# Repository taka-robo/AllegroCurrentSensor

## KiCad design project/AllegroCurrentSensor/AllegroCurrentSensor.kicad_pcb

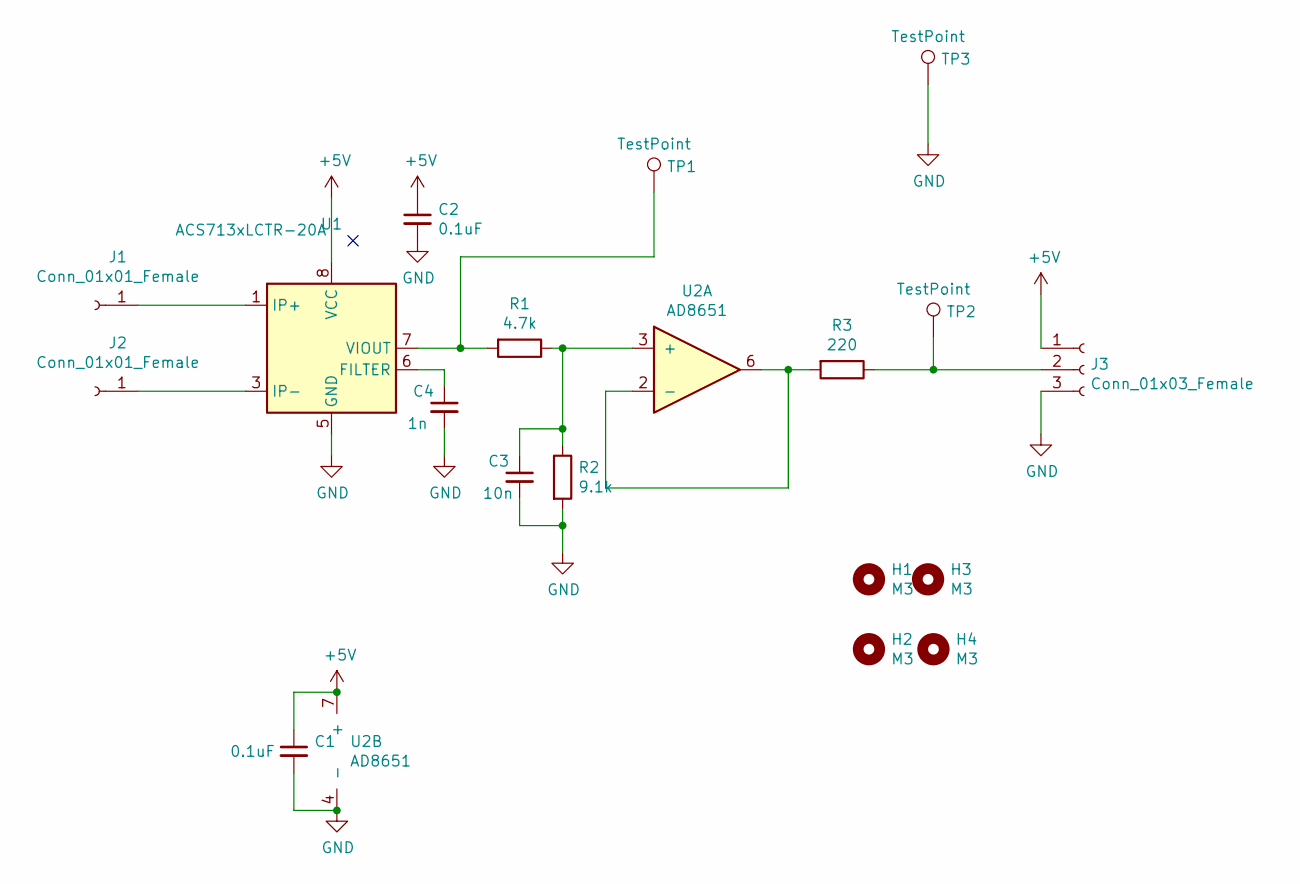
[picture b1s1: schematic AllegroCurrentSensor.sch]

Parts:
C1, C2: 0.1uF; C_0603_1608Metric_Pad1.08x0.95mm_HandSolder
C3: 10n; C_0603_1608Metric_Pad1.08x0.95mm_HandSolder
C4: 1n; C_0603_1608Metric_Pad1.08x0.95mm_HandSolder
H1, H2, H3, H4: M3; MountingHole_3.2mm_M3
J1, J2: Conn_01x01_Female; TestPoint_Pad_4.0x4.0mm
J3: Conn_01x03_Female; PinHeader_1x03_P2.54mm_Vertical
R1: 4.7k; R_0603_1608Metric_Pad0.98x0.95mm_HandSolder
R2: 9.1k; R_0603_1608Metric_Pad0.98x0.95mm_HandSolder
R3: 220; R_0603_1608Metric_Pad0.98x0.95mm_HandSolder
TP1, TP2, TP3: TestPoint; Pin_D0.7mm_L6.5mm_W1.8mm_FlatFork
U1: ACS713xLCTR-20A; SOIC-8_3.9x4.9mm_P1.27mm
U2: AD8651; SOIC-8_3.9x4.9mm_P1.27mm

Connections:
+5V: C1.1, C2.1, J3.1, U1.8 (VCC), U2.7 (+)
GND: C1.2, C2.2, C3.2, C4.2, J3.3, R2.2, TP3.1, U1.5 (GND), U2.4 (-)
unnamed: C3.1, R1.1, R2.1, U2.3 (+)
unnamed: C4.1, U1.6 (FILTER)
unnamed: J1.1, U1.1 (IP+), U1.2 (IP+)
unnamed: J2.1, U1.3 (IP-), U1.4 (IP-)
unnamed: J3.2, R3.1, TP2.1
unnamed: R1.2, TP1.1, U1.7 (VIOUT)
unnamed: R3.2, U2.2 (-), U2.6

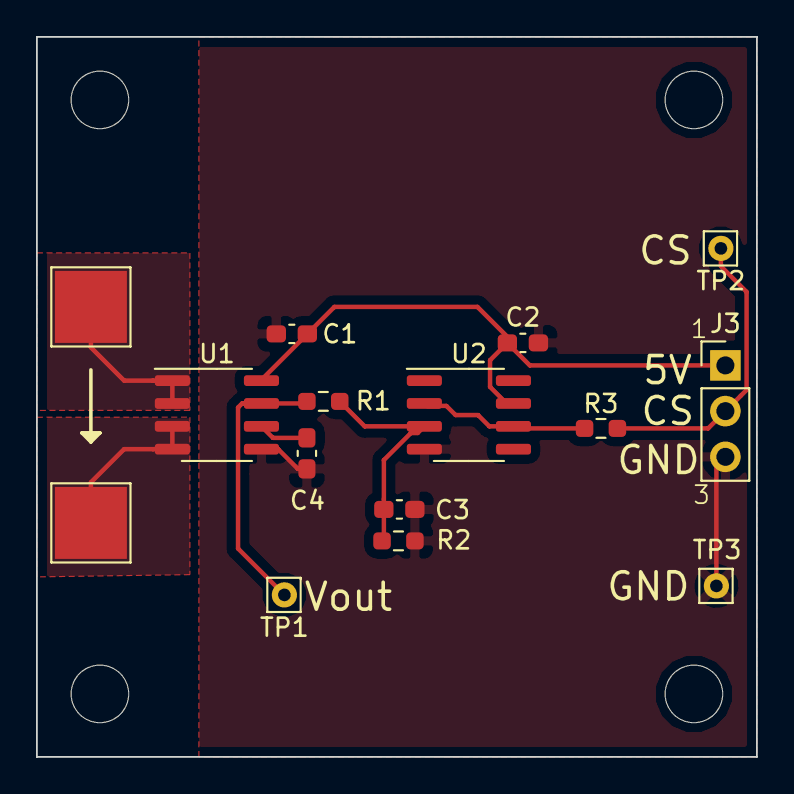
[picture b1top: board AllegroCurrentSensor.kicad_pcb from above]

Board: 2 copper layers, 40.0 x 40.0 mm, 19 parts (0 on the bottom side), 9 nets.

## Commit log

2021-01-16 ver1.0
2021-01-16 発注用データ作成
2021-01-16 update ignore
